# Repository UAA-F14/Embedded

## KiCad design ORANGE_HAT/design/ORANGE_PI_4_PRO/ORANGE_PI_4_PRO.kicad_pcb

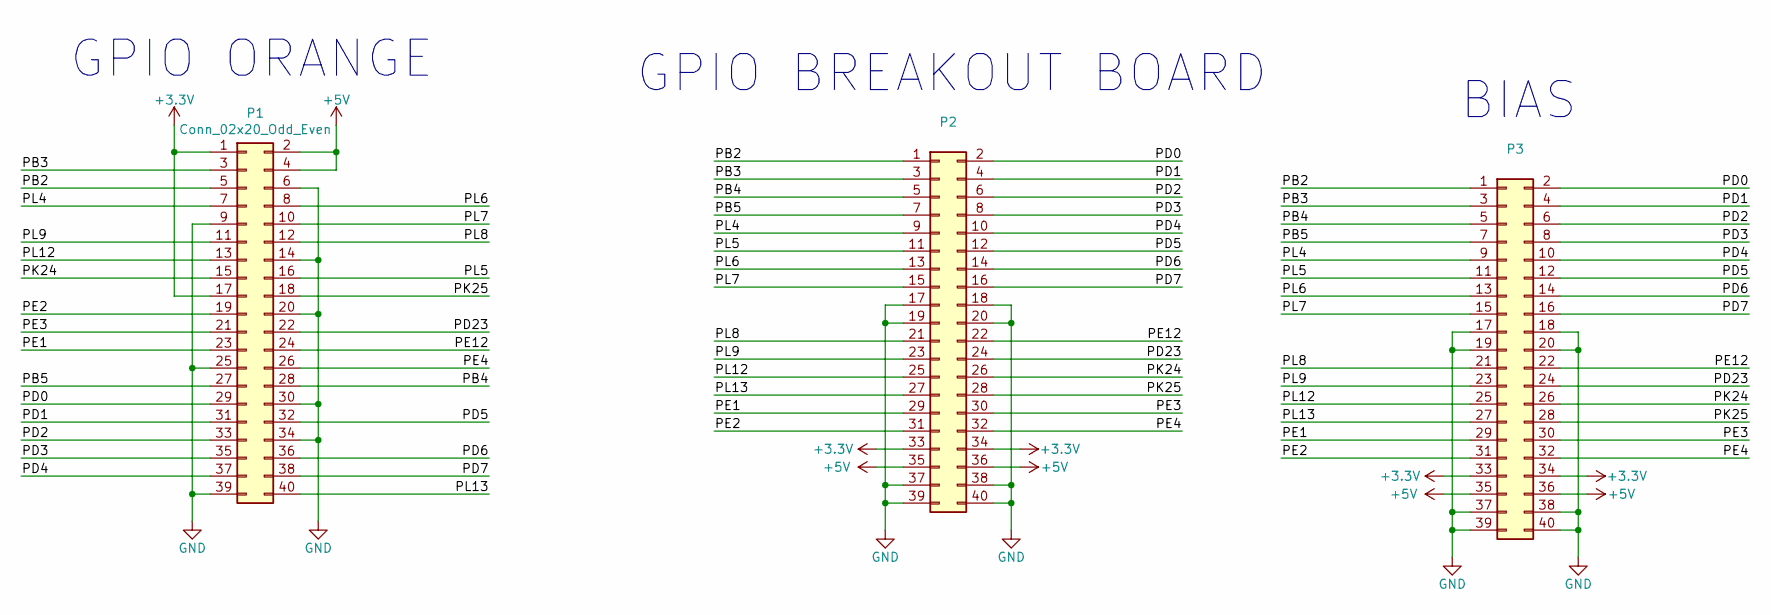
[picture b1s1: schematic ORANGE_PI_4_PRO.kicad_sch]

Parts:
P1, P2, P3: Conn_02x20_Odd_Even; PinSocket_2x20_P2.54mm_Vertical

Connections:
+3.3V: P1.1, P1.17, P2.33, P2.34, P3.33, P3.34
+5V: P1.2, P1.4, P2.35, P2.36, P3.35, P3.36
/PB2: P1.5, P2.1, P3.1
/PB3: P1.3, P2.3, P3.3
/PB4: P1.28, P2.5, P3.5
/PB5: P1.27, P2.7, P3.7
/PD0: P1.29, P2.2, P3.2
/PD1: P1.31, P2.4, P3.4
/PD2: P1.33, P2.6, P3.6
/PD3: P1.35, P2.8, P3.8
/PD4: P1.37, P2.10, P3.10
/PD5: P1.32, P2.12, P3.12
/PD6: P1.36, P2.14, P3.14
/PD7: P1.38, P2.16, P3.16
/PD23: P1.22, P2.24, P3.24
/PE1: P1.23, P2.29, P3.29
/PE2: P1.19, P2.31, P3.31
/PE3: P1.21, P2.30, P3.30
/PE4: P1.26, P2.32, P3.32
/PE12: P1.24, P2.22, P3.22
/PK24: P1.15, P2.26, P3.26
/PK25: P1.18, P2.28, P3.28
/PL4: P1.7, P2.9, P3.9
/PL5: P1.16, P2.11, P3.11
/PL6: P1.8, P2.13, P3.13
/PL7: P1.10, P2.15, P3.15
/PL8: P1.12, P2.21, P3.21
/PL9: P1.11, P2.23, P3.23
/PL12: P1.13, P2.25, P3.25
/PL13: P1.40, P2.27, P3.27
GND: P1.6, P1.9, P1.14, P1.20, P1.25, P1.30, P1.34, P1.39, P2.17, P2.18, P2.19, P2.20, P2.37, P2.38, P2.39, P2.40, P3.17, P3.18, P3.19, P3.20, P3.37, P3.38, P3.39, P3.40

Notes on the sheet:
GPIO BREAKOUT BOARD
BIAS
GPIO ORANGE

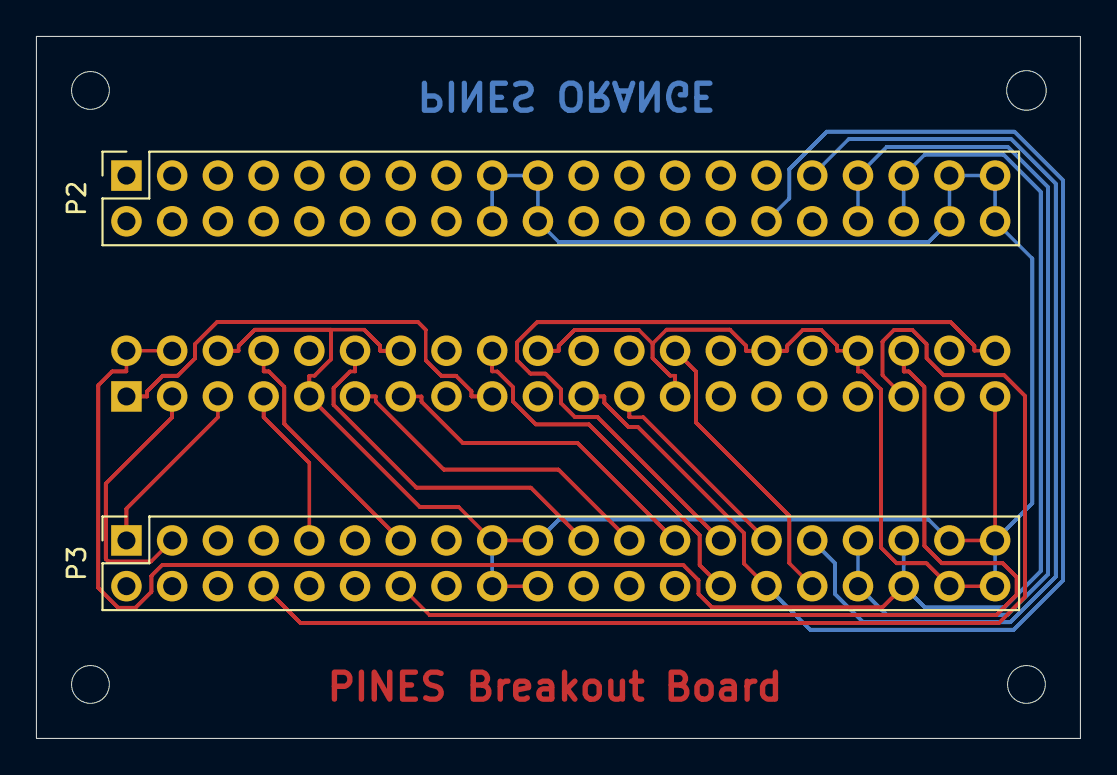
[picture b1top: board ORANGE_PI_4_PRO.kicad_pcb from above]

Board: 2 copper layers, 58.0 x 39.0 mm, 7 parts (1 on the bottom side), 31 nets.

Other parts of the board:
H1, H3, H4: MountingHole_2.1mm
H2: MountingHole_2.2mm_M2
